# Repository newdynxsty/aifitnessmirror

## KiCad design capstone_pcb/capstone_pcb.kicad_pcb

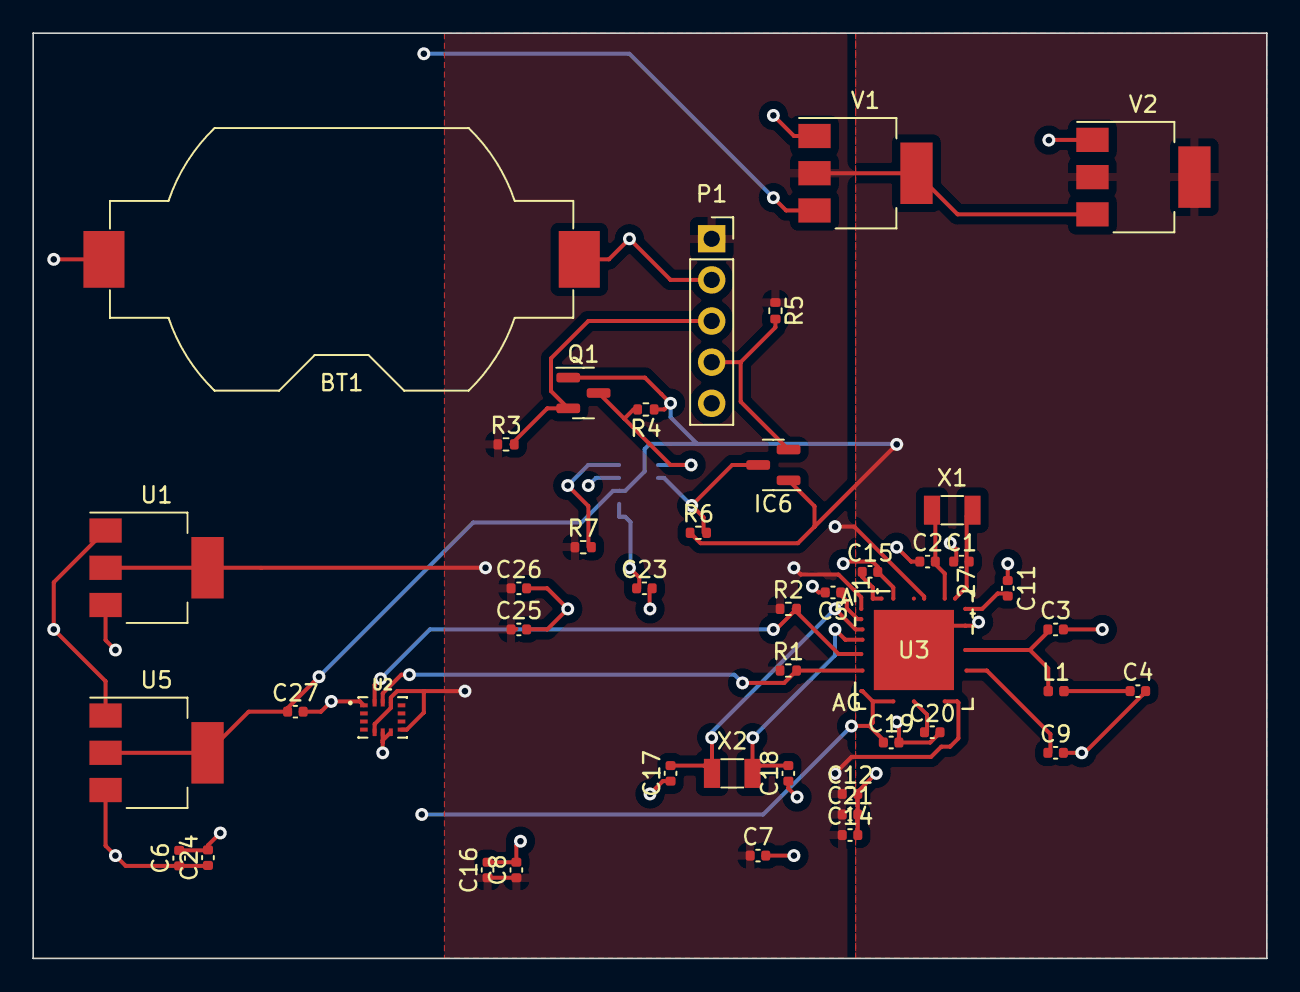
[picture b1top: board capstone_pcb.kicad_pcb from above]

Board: 4 copper layers, 76.2 x 57.2 mm, 45 parts (1 on the bottom side), 23 nets.

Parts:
BT1: Battery_Cell; BatteryHolder_Keystone_1058_1x2032
C1, C2, C17, C18: 12pF; C_0402_1005Metric
C3: 0.8pF; C_0402_1005Metric
C4: 0.5pF; C_0402_1005Metric
C5, C7, C8, C12, C16, C21: 100nF; C_0402_1005Metric
C6, C19, C20: 4.7uF; C_0402_1005Metric
C9: 820pF; C_0402_1005Metric
C11: 100pF; C_0402_1005Metric
C14, C15: 1.0uF; C_0402_1005Metric
C23, C26: 0.1uF; C_0402_1005Metric
C24, C27: 1uF; C_0402_1005Metric
C25: 47uF; C_0402_1005Metric
IC6: BSS138; SOT-23
L1: 4.7nH; L_0402_1005Metric
P1: MHDR1X5; PinSocket_1x05_P2.54mm_Vertical
Q1: BSS138; SOT-23
R1, R2: 4.7k; R_0402_1005Metric
R3, R4, R5, R6, R7: 10K; R_0402_1005Metric
U1: AMS1117-3.3; SOT-223-3_TabPin2
U2: BMI270; XDCR_BMI270
U3: NRF52840-QIAA-R; nrf52840_qiaa_r
U4: MAX30102EFD+T; XDCR_MAX30101EFD_
U5: AMS1117-1.8; SOT-223-3_TabPin2
V1: 3.3V; SOT-223-3_TabPin2
V2: 1.8V; SOT-223-3_TabPin2
X1: 32MHz; Crystal_SMD_3215-2Pin_3.2x1.5mm
X2: 32.768kHz; Crystal_SMD_3215-2Pin_3.2x1.5mm

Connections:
+1.8V: C27.1, IC6.1 (G), Q1.1 (G), R4.1, R6.1, U4.11 (VDD), U5.2 (VO), V2.2 (VO)
+3.3V: C7.1, C8.1, C12.1, C14.1, C16.1, C21.1, C25.1, C26.1, P1.1, R1.1, R2.1, R3.1, R5.1, R7.1, U1.2 (VO), U2.5 (VDDIO), U2.8 (VDD), U2.12 (CSB), U3.A22 (VDD), U3.AD14 (VDD), U3.AD23 (VDD), U3.B1 (VDD), V1.2 (VO), V2.3 (VI)
+5V: BT1.1 (+), C6.1, C19.1, C24.1, U1.3 (VI), U3.AD2 (VBUS), U3.W1 (VDD), U3.Y2 (VDDH), U5.3 (VI), V1.3 (VI)
/ASCL: P1.3, Q1.2 (S), R3.2
/ASDA: IC6.2 (S), P1.4, R5.2
/BSCL: Q1.3 (D), R4.2, U4.2 (SCL)
/BSDA: IC6.3 (D), R6.2, U4.3 (SDA)
/DEC4 6: C15.1, U3.B5 (DEC4), U3.E24 (DEC2)
/RF: C4.1, L1.2
/SCL: R1.2, U2.13 (SCX), U3.P2 (P1.08)
/SDA: R2.2, U2.14 (SDX), U3.N1 (P0.08)
Earth: BT1.2 (-), C1.1, C2.1, C3.2, C4.2, C5.2, C6.2, C7.2, C8.2, C9.2, C11.1, C12.2, C14.2, C15.2, C16.2, C17.1, C18.1, C19.2, C20.2, C21.2, C23.2, C24.2, C25.2, C26.2, C27.2, P1.2, U1.1 (GND), U2.1 (SDO), U2.6 (GNDIO), U2.7 (GND), U3.74 (VSS), U3.B7 (VSS), U3.F23 (VSS_PA), U4.12 (GND), U5.1 (GND), V1.1 (GND), V2.1 (GND)
unnamed: C23.1, U4.9 (VLED+), U4.10 (VLED+)
unnamed: C3.1, L1.1, U3.H23 (ANT)
unnamed: C5.1, U3.C1 (DEC1)
unnamed: C11.2, U3.D23 (DEC3)
unnamed: C9.1, U3.N24 (DEC5)
unnamed: C20.1, U3.AC5 (DECUSB)
unnamed: C17.2, U3.D2 (P0.00/XL1), X2.2
unnamed: C18.2, U3.F2 (P0.01/XL2), X2.1
unnamed: C1.2, U3.B24 (XC1), X1.1
unnamed: C2.2, U3.A23 (XC2), X1.2
unnamed: R7.2, U4.13 (*INT)

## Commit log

2026-01-13 Adding library installation
2026-01-15 adding to github
2026-01-15 adding situp videos for training
2026-01-15 Changing from MediaPipe to MoveNet
2026-01-15 Optimize testing
2026-02-12 adding standing dataset
2026-03-05 pcb/
2026-03-06 pcb schematic
2026-03-06 pcb backups
2026-03-12 Adding repcounter
2026-03-12 PCB layout complete
2026-03-12 Add test file to footprints directory
2026-03-13 nrf footprint
2026-03-13 update pcb
2026-03-13 Initial attempt at repcounter
2026-04-07 Add Repetition Count Folder
2026-04-08 Removing old rep counter folder
2026-04-09 Adding jumping jacks data to repcounter
2026-04-09 Adding situps
2026-04-09 Pushups
2026-04-09 Adding lunges
2026-04-09 Purging standing class for lunge
2026-04-17 WIP Rep Counter Debugging
2026-04-17 Delete capstone_pcb directory
    pcb stored at https://github.com/austish/NuvoMotionPCB
